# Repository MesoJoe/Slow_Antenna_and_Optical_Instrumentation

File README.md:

# Electric Field Change Measurements and Lightning Observations

This repository contains circuit designs and software developed for research involving slow antennas and optical verification of long continuing current (LCC) lightning. Additionally, designs for a novel diametrically loaded loop antenna for lightning research and an Active Bias Integrator (ABI) charge amplifier for slow antenna applications are presented. Much of this work is described in 'DESIGN AND IMPLEMENTATION OF A SLOW ANTENNA FOR OBSERVING LONG CONTINUING CURRENT LIGHTNING', Master's Thesis. 

## Repository Contents

- **ABI Charge Amplifier Circuit** – Active Bias Integrator (ABI) charge amplifier design (adapted from Alnasser).
  - **Contents:** KiCad circuit design files.

- **BAS_CAM Code** – Basler camera acquisition software.
  - **Contents:** C++ code and Makefile for Basler camera operation.

- **DAQ Code** – Data acquisition software for recording slow antenna measurements.
  - **Contents:** Python code and environment for the MCC 128 DAQ on Raspberry Pi 4.

- **Diametric Loaded Loop Circuit** – Circuit design and simulations for a diametrically loaded loop antenna (adapted from Kanda).
  - **Contents:** KiCad circuit design files.

- **PI_CAM_code** – Raspberry Pi camera acquisition software.
  - **Contents:** Raspberry Pi camera code for automatic continuous recording upon startup or reboot.

- **Slow Antenna Circuit** – Conventional slow antenna charge amplifier circuit design and simulations.

## Author

**Joseph Berry**  

University of Oklahoma  

School of Electrical and Computer Engineering  

School of Meteorology

## Citation

If you use any circuit designs, software, or instrumentation
from this repository in your research or publications,
please cite this repository. Thanks! 

### American Meteorological Society (AMS)

Berry, J., 2026: *Slow Antenna and Optical Instrumentation*.
GitHub repository, University of Oklahoma.
https://github.com/MesoJoe/Slow_Antenna_and_Optical_Instrumentation

### IEEE

J. Berry, "Slow Antenna and Optical Instrumentation,"
GitHub repository, 2026. [Online]. Available:
https://github.com/MesoJoe/Slow_Antenna_and_Optical_Instrumentation

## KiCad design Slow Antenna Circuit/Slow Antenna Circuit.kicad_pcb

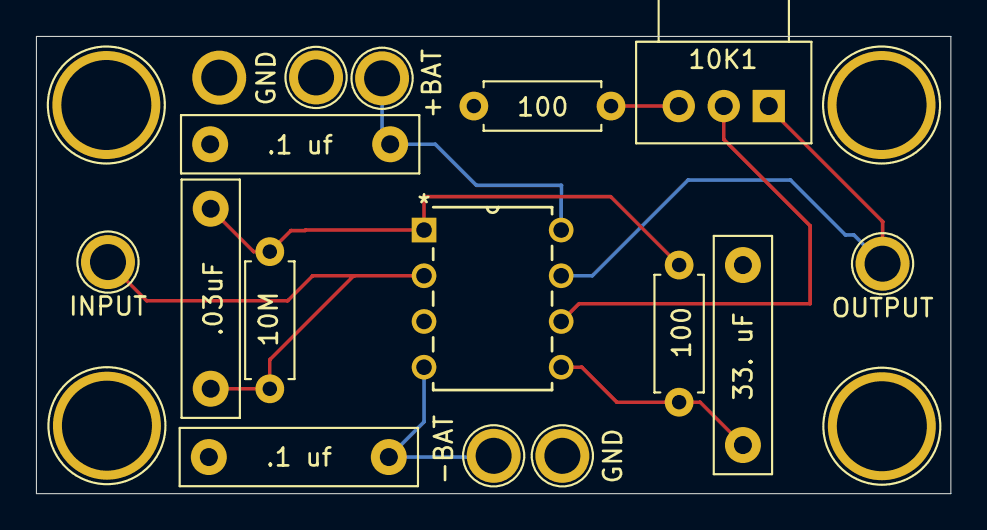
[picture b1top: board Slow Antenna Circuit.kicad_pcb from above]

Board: 2 copper layers, 50.8 x 25.4 mm, 19 parts (0 on the bottom side), 9 nets.

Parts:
10K1: R_Potentiometer; Potentiometer_Alps_RK09Y11_Single_Horizontal
10M: 10M; R_Axial_DIN0207_L6.3mm_D2.5mm_P7.62mm_Horizontal
100, 100#2: 100; R_Axial_DIN0207_L6.3mm_D2.5mm_P7.62mm_Horizontal
.03uF: .03 uF; C_Rect_L13.0mm_W3.0mm_P10.00mm_FKS3_FKP3_MKS4
C2: 33. uF; C_Rect_L13.0mm_W3.0mm_P10.00mm_FKS3_FKP3_MKS4
C3, C4: .1 uf; C_Rect_L13.0mm_W3.0mm_P10.00mm_FKS3_FKP3_MKS4
TP1: OUTPUT; TestPoint_Plated_Hole_D2.0mm
TP2: INPUT; TestPoint_Plated_Hole_D2.0mm
TP3: +BAT; TestPoint_Plated_Hole_D2.0mm
TP4: -BAT; TestPoint_Plated_Hole_D2.0mm
TP5, TP6: GND; TestPoint_Plated_Hole_D2.0mm
TP8, TP9, TP10, TP11: MNT; TestPoint_Plated_Hole_D5.0mm
U1: OPA2277; P8

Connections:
GND: 100#2.2, C2.1, C3.1, C4.1, TP5.1, TP6.1, TP8.1, TP9.1, TP10.1, TP11.1, U1.3 (+)
unnamed: 10K1.1, TP1.1, U1.7
unnamed: 10K1.3, 100#2.1
unnamed: 10M.1, 100.2, .03uF.1, U1.1
unnamed: 10M.2, .03uF.2, TP2.1, U1.2 (-)
unnamed: 100.1, C2.2, U1.5 (+)
unnamed: 10K1.2, U1.6 (-)
unnamed: C4.2, TP3.1, U1.8 (V+)
unnamed: C3.2, TP4.1, U1.4 (V-)

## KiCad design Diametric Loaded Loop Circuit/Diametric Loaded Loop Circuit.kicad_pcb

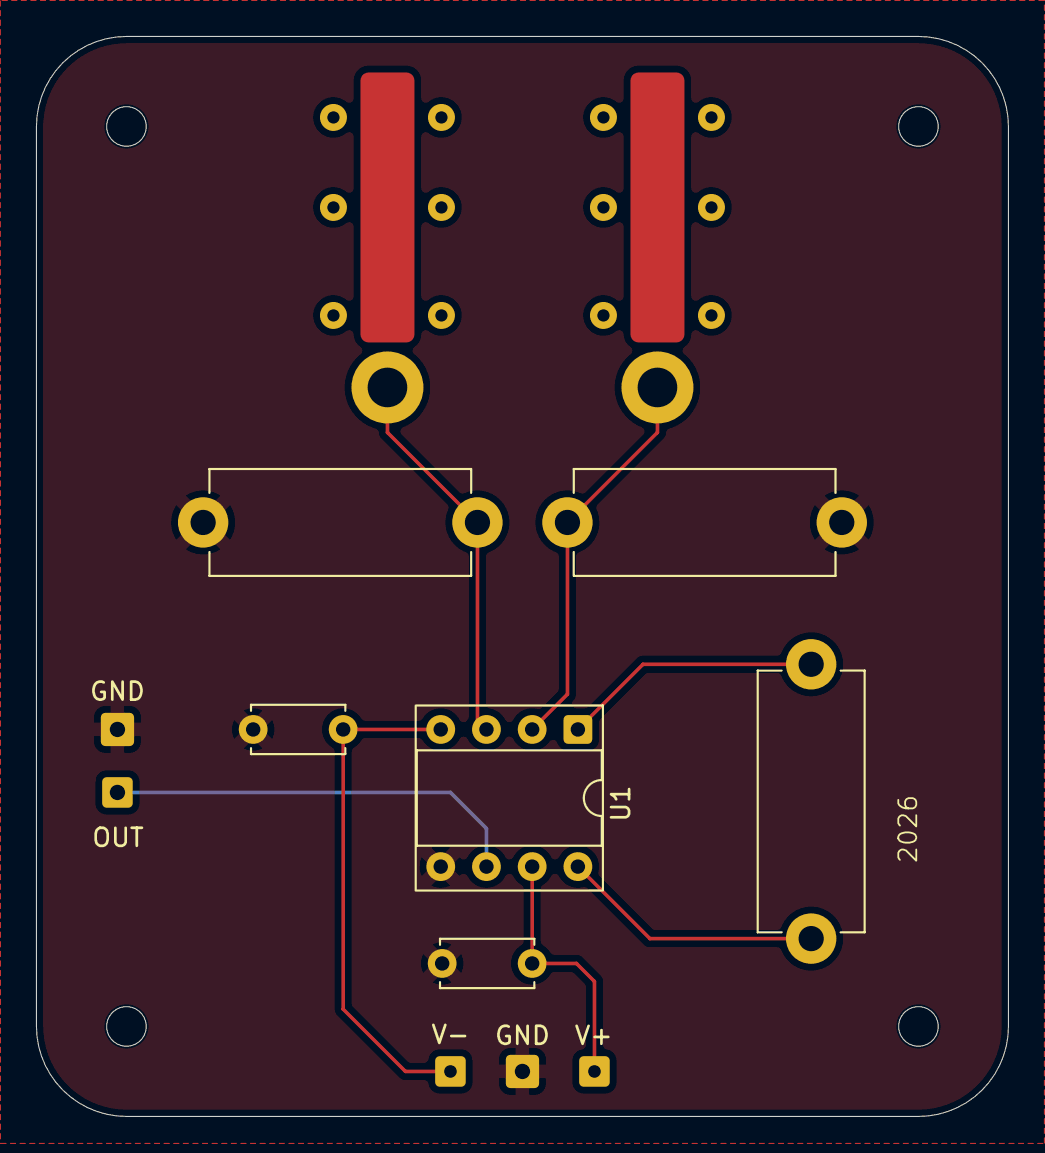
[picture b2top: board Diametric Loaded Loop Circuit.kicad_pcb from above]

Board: 2 copper layers, 54.0 x 60.0 mm, 14 parts (0 on the bottom side), 8 nets.

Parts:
C0.1uF1, C0.1uF2: 0.1uF; C_Disc_D5.0mm_W2.5mm_P5.00mm
GND: MountingHole_Pad; SolderWire-0.25sqmm_1x01_D0.65mm_OD1.7mm
H1, H2, H3, H4: MountingHole; MountingHole_2.2mm_M2
OUT: Conn_01x01; SolderWire-0.15sqmm_1x01_D0.5mm_OD1.5mm
R1MEG1, R1MEG2: 1MEG; R_Axial_DIN0614_L14.3mm_D5.7mm_P15.24mm_Horizontal
R560: 560; R_Axial_DIN0614_L14.3mm_D5.7mm_P15.24mm_Horizontal
U1: INA128; DIP-8_W7.62mm_Socket
V+: Conn_01x01; SolderWire-0.15sqmm_1x01_D0.5mm_OD1.5mm
V-: Conn_01x01; SolderWire-0.15sqmm_1x01_D0.5mm_OD1.5mm

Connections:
GND: C0.1uF1.2, C0.1uF2.2, GND.1 (1_1), R1MEG1.1, R1MEG2.2, U1.5 (Ref)
unnamed: R1MEG1.2, U1.3 (+)
unnamed: R1MEG2.1, U1.2 (-)
unnamed: C0.1uF1.1, U1.7 (V+), V+.1 (Pin_1_1)
unnamed: C0.1uF2.1, U1.4 (V-), V-.1 (Pin_1_1)
unnamed: OUT.1 (Pin_1_1), U1.6
unnamed: R560.1, U1.1 (Rg)
unnamed: R560.2, U1.8 (Rg)

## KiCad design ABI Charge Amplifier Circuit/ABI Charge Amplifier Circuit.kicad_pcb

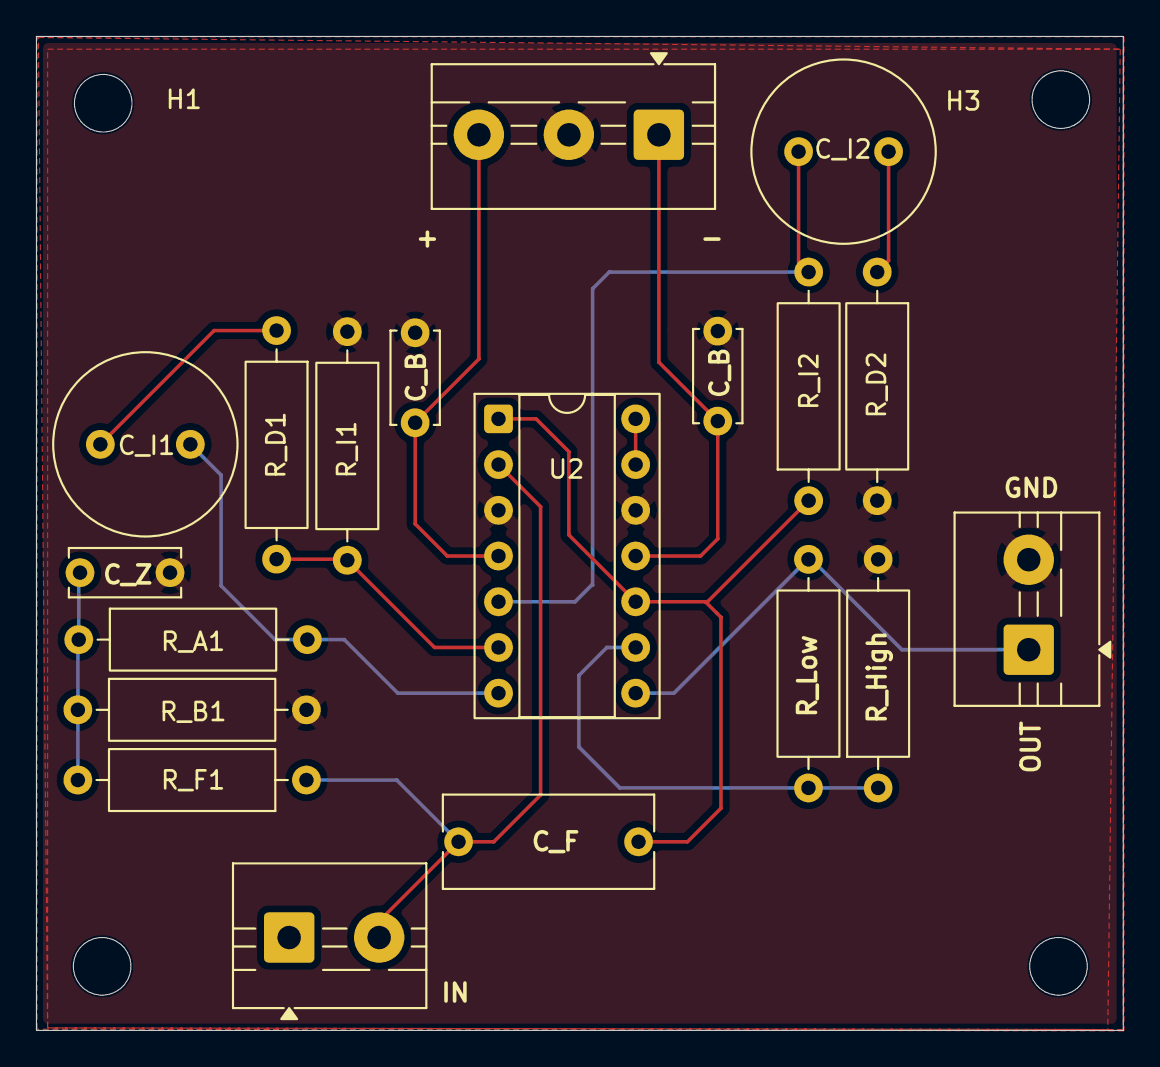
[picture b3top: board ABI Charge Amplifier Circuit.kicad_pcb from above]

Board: 2 copper layers, 60.4 x 55.2 mm, 23 parts (0 on the bottom side), 14 nets.

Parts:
C_F1: 33nF; C_Rect_L11.5mm_W5.0mm_P10.00mm_MKT
C_I1, C_I2: 100uF; C_Radial_D10.0mm_H20.0mm_P5.00mm
C_Z1: 10nF; C_Disc_D6.0mm_W2.5mm_P5.00mm
Cbat1, Cbat2: 0.1uF; C_Disc_D5.0mm_W2.5mm_P5.00mm
H1, H2, H3, H4: MountingHole; MountingHole_3.2mm_M3
IN: INPUT; TerminalBlock_MaiXu_MX126-5.0-02P_1x02_P5.00mm
J1: BATTERY; TerminalBlock_MaiXu_MX126-5.0-03P_1x03_P5.00mm
OUT: OUTPUT; TerminalBlock_MaiXu_MX126-5.0-02P_1x02_P5.00mm
R_A1: 2k2; R_Axial_DIN0309_L9.0mm_D3.2mm_P12.70mm_Horizontal
R_B1: 4k3; R_Axial_DIN0309_L9.0mm_D3.2mm_P12.70mm_Horizontal
R_D1, R_D2: 510k; R_Axial_DIN0309_L9.0mm_D3.2mm_P12.70mm_Horizontal
R_F1: 3M3; R_Axial_DIN0309_L9.0mm_D3.2mm_P12.70mm_Horizontal
R_High: 100; R_Axial_DIN0309_L9.0mm_D3.2mm_P12.70mm_Horizontal
R_I1, R_I2: 1M; R_Axial_DIN0309_L9.0mm_D3.2mm_P12.70mm_Horizontal
R_Low: 2k2; R_Axial_DIN0309_L9.0mm_D3.2mm_P12.70mm_Horizontal
U2: OPA4376; DIP-14_W7.62mm_Socket

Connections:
GND: C_Z1.2, Cbat1.1, Cbat2.2, J1.2, OUT.2, R_B1.2, R_D2.2, R_High.2, R_I1.1, U2.3 (+), U2.12 (+)
unnamed: C_I1.1, R_A1.2, U2.7
unnamed: C_I1.2, R_D1.1
unnamed: C_I2.2, R_D2.1
unnamed: C_Z1.1, R_A1.1, R_B1.1, R_F1.2
unnamed: Cbat2.1, J1.1, U2.11 (V-)
unnamed: Cbat1.2, J1.3, U2.4 (V+)
unnamed: C_F1.1, IN.2 (Pin_2_2), R_F1.1, U2.2 (-)
unnamed: OUT.1, R_Low.1, U2.8
unnamed: C_I2.1, R_I2.2, U2.5 (+)
unnamed: R_D1.2, R_I1.2, U2.6 (-)
unnamed: C_F1.2, R_I2.1, U2.1, U2.10 (+)
unnamed: R_High.1, R_Low.2, U2.9 (-)
unnamed: U2.13 (-), U2.14
